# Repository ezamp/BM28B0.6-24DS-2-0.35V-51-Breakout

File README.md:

# BM28B0.6-24DS-2-0.35V-51-Breakout
Breakout for BM28B0.6-24DS/2-0.35V(51) connector

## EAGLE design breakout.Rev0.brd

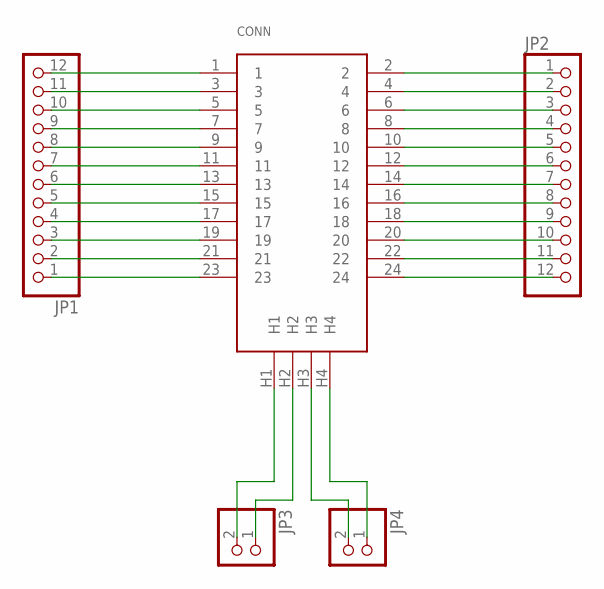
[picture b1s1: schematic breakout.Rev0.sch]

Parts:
CONN: BM28B0.6-24DS/2-0.35V(51)
JP1, JP2: PINHD-1X12; 1X12
JP3, JP4: PINHD-1X2; 1X02

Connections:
unnamed: CONN.2, JP2.1
unnamed: CONN.4, JP2.2
unnamed: CONN.6, JP2.3
unnamed: CONN.8, JP2.4
unnamed: CONN.10, JP2.5
unnamed: CONN.12, JP2.6
unnamed: CONN.14, JP2.7
unnamed: CONN.16, JP2.8
unnamed: CONN.18, JP2.9
unnamed: CONN.20, JP2.10
unnamed: CONN.22, JP2.11
unnamed: CONN.24, JP2.12
unnamed: CONN.H3, JP4.2
unnamed: CONN.H4, JP4.1
unnamed: CONN.H2, JP3.1
unnamed: CONN.H1, JP3.2
unnamed: CONN.23, JP1.1
unnamed: CONN.21, JP1.2
unnamed: CONN.19, JP1.3
unnamed: CONN.17, JP1.4
unnamed: CONN.15, JP1.5
unnamed: CONN.13, JP1.6
unnamed: CONN.11, JP1.7
unnamed: CONN.9, JP1.8
unnamed: CONN.7, JP1.9
unnamed: CONN.5, JP1.10
unnamed: CONN.3, JP1.11
unnamed: CONN.1, JP1.12

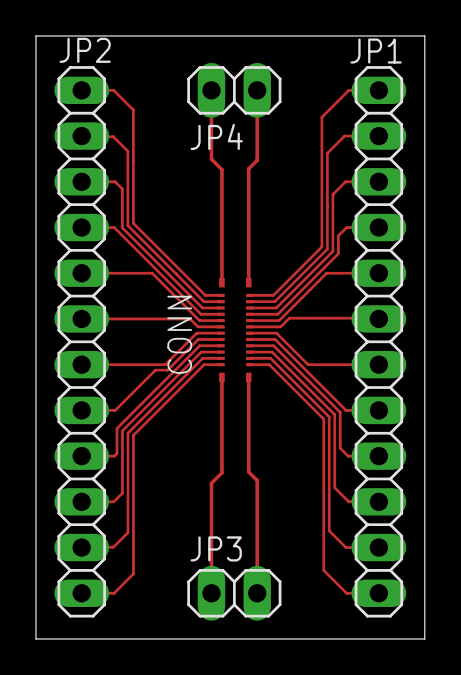
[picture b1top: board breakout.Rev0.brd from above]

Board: 2 copper layers, 21.6 x 33.5 mm, 5 parts (0 on the bottom side), 28 nets.
